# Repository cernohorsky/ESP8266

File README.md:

# ESP8266
ESP8266 breakout board with TPS63030 buck-boost convertor and MOSFET on GPIO15. Very small size.

<b>ToDo:</b><br>
Change inductor to Wurth MAPI<br>
Change convertor to TPS63021<br>

#TPS63030, #ESP8266, #ESP12

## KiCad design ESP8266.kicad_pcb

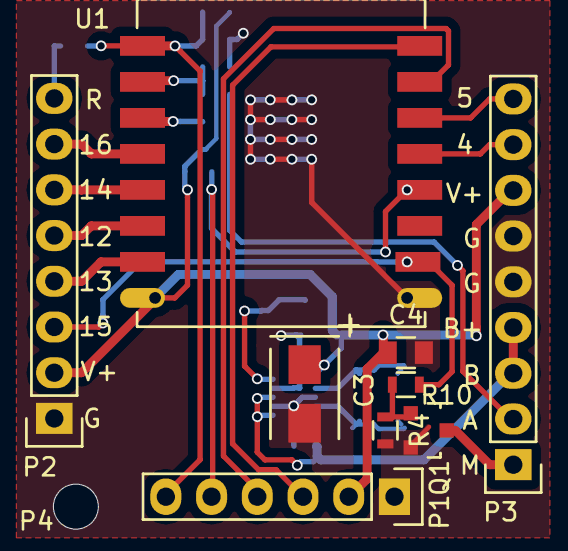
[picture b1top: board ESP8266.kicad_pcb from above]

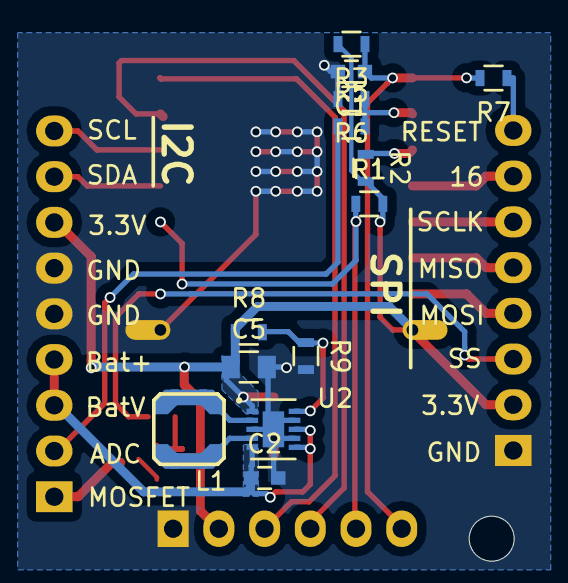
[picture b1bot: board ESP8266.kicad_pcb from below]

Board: 2 copper layers, 23 parts (13 on the bottom side), 23 nets.

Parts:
C1: 470p; C_0603
C2: 2u2; C_0603
C3: 100u; TantalC_SizeB_EIA-3528_Wave
C4, C5: 10u; C_0805
L1: INDUCTOR; LPS4018
P1: CONN_01X06; Pin_Header_Straight_1x06
P2: CONN_01X08; Pin_Header_Straight_1x08
P3: CONN_01X09; Pin_Header_Straight_1x09
P4: CONN_01X01; MountingHole_2.5mm
Q1: Q_NMOS_GSD; SOT-23
R1, R2, R3, R4: 12k; R_0603
R5: 330k; R_0603
R6: 100k; R_0603
R7: 470R; R_0603
R8: 560k 1%; R_0603
R9: 100k 1%; R_0603
R10: 1k; R_0603
U1: ESP-07v2
U2: TPS63030; DSK-10Pin-VSON

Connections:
+3V3: C3.1, C4.1, C5.1, P1.2, P2.2, P3.7, R1.2, R2.2, R3.2, R8.1, U1.8, U2.1
/ADC: R5.2, R6.1, U1.2
/ADC-EX: P3.2, R5.1
/EN: R2.1, U1.3
/GPIO0: P1.5, R1.1, U1.12
/GPIO4: P3.8, U1.13
/GPIO5: P3.9, U1.14
/GPIO12: P2.5, U1.6
/GPIO13: P2.4, U1.7
/GPIO14: P2.6, U1.5
/GPIO15: P2.3, R10.2, U1.10
/GPIO16: P2.7, U1.4
/MOSFET: P3.1, Q1.3
/RES: C1.1, P1.6, R3.1, R7.2, U1.1
/RX: P1.4, U1.15
/TX: P1.3, U1.16
GND: C1.2, C2.2, C3.2, C4.2, C5.2, P1.1, P2.1, P3.5, P3.6, P4.1, Q1.2, R4.2, R6.2, R9.2, U1.9, U2.3, U2.7, U2.9, U2.11
unnamed: L1.1, U2.4
unnamed: L1.2, U2.2
unnamed: P2.8, R7.1
unnamed: Q1.1, R4.1, R10.1
unnamed: R8.2, R9.1, U2.10
VCC: C2.1, P3.3, P3.4, U2.5, U2.6, U2.8

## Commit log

2019-03-14 Final v1.0
2019-03-22 Added lib files
2019-04-06 Changed ToDo
